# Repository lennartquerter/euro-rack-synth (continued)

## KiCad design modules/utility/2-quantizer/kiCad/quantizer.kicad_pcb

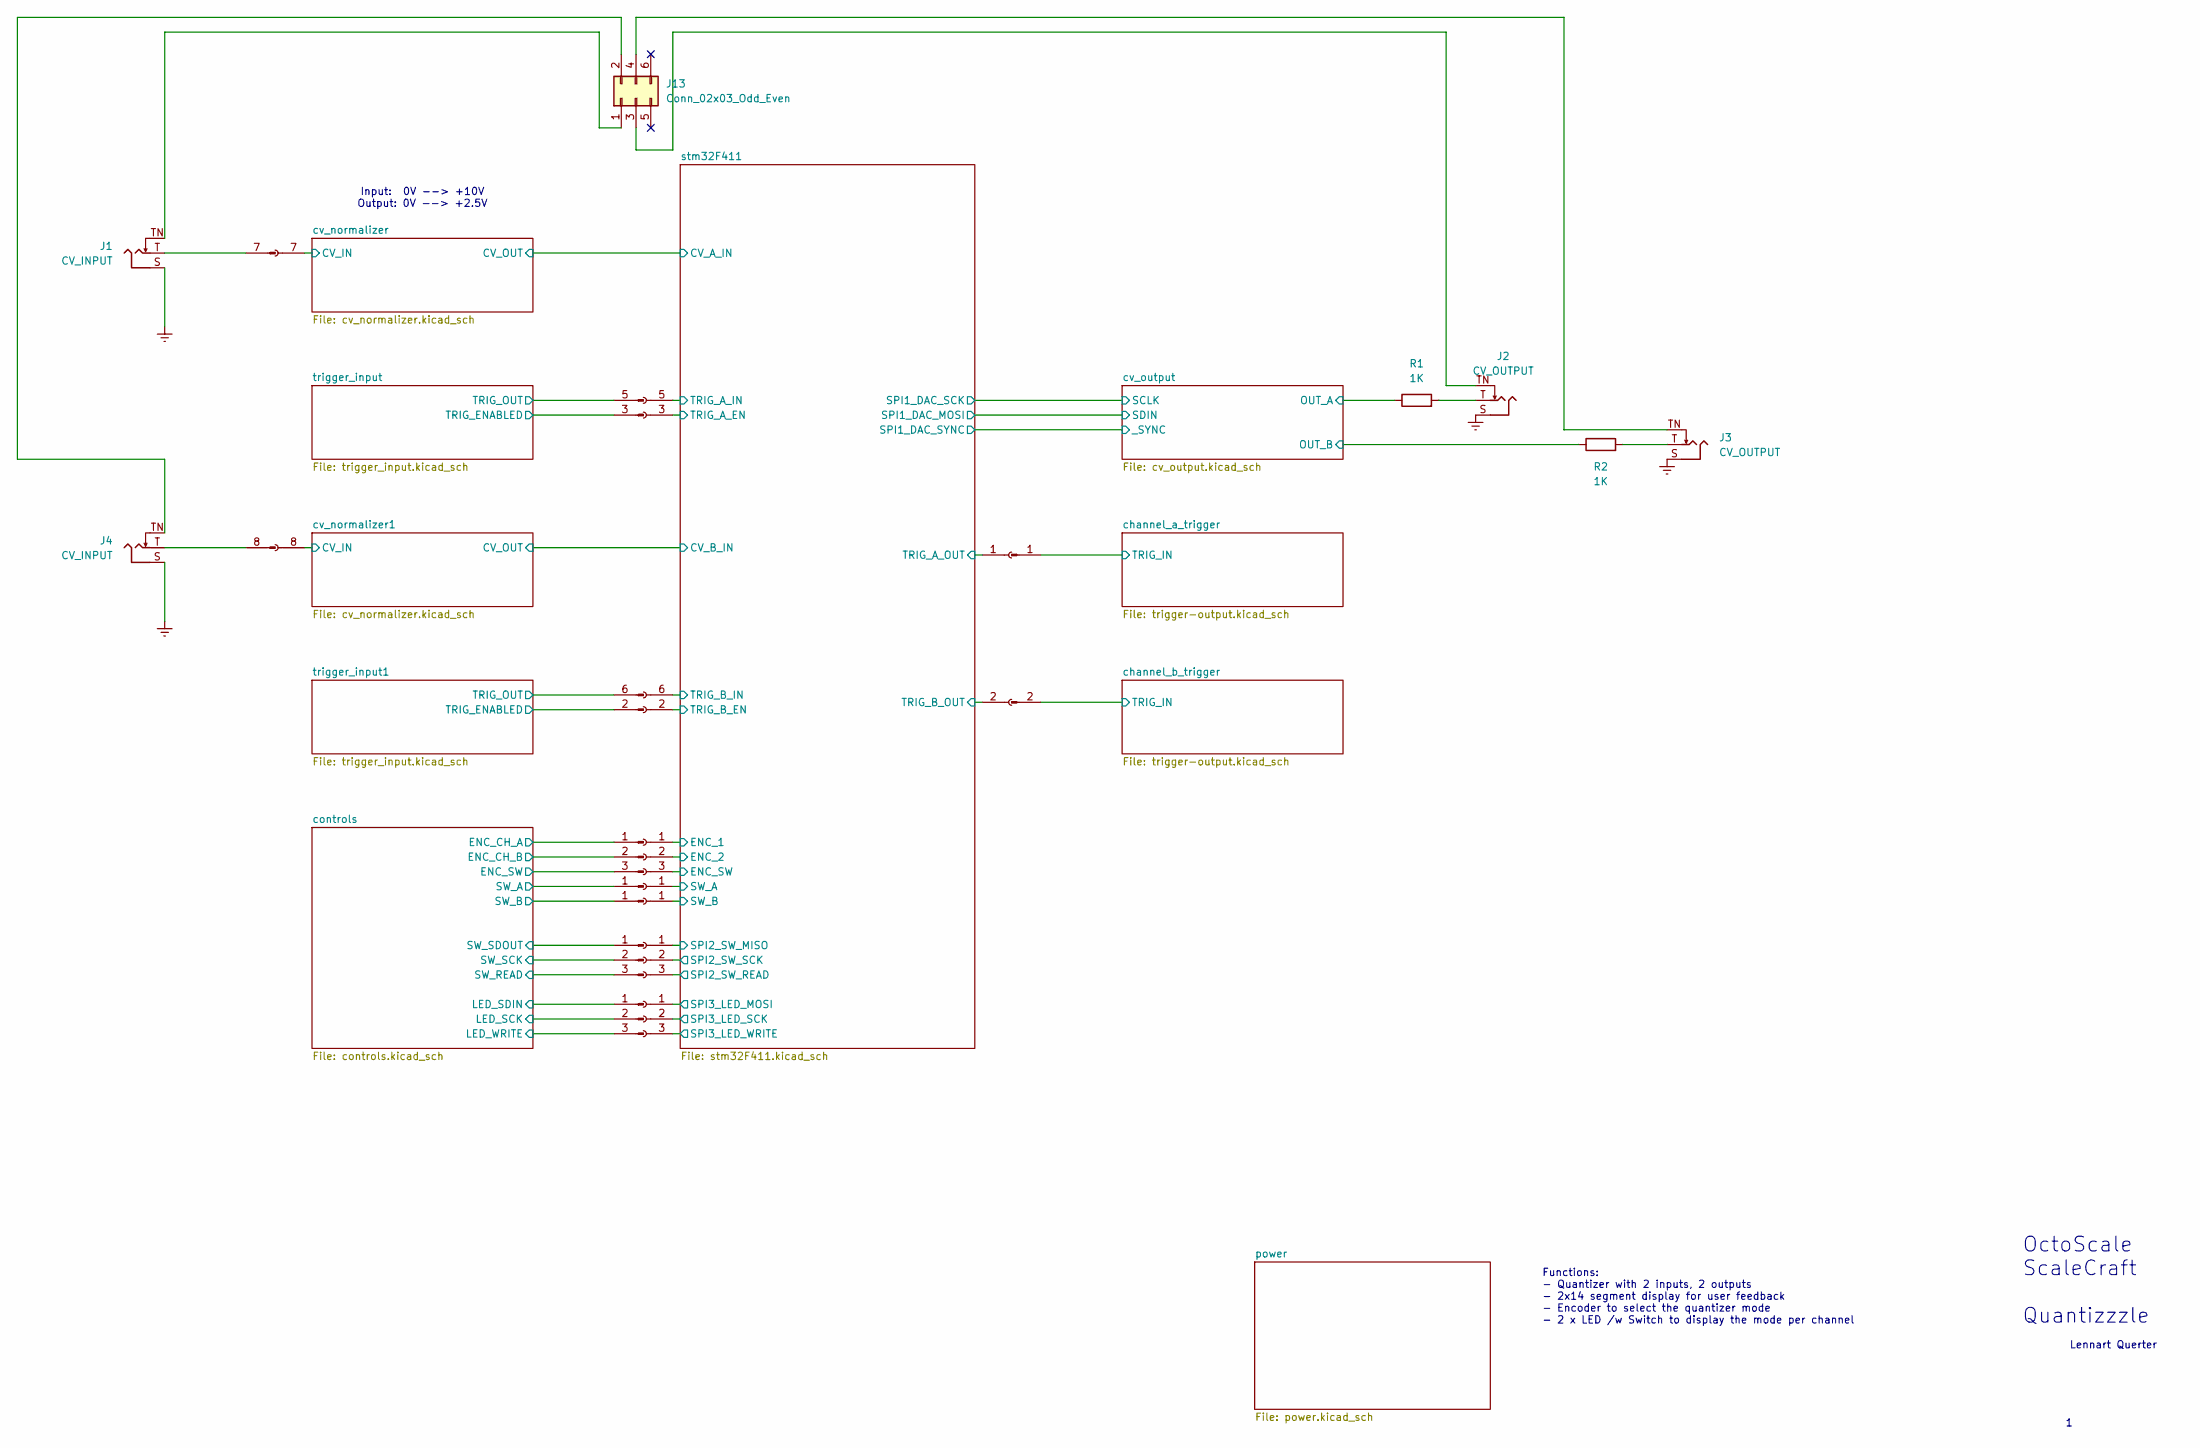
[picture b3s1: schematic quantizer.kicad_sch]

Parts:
J1, J4: CV_INPUT; Jack_3.5mm_QingPu_WQP-PJ398SM_Vertical_CircularHoles
J2, J3: CV_OUTPUT; Jack_3.5mm_QingPu_WQP-PJ398SM_Vertical_CircularHoles
J13: Conn_02x03_Odd_Even; PinHeader_2x03_P2.54mm_Vertical
R1, R2: 1K; R_0805_2012Metric_Pad1.20x1.40mm_HandSolder
XP1: Conn_01x08_Pin; PinHeader_1x08_P2.54mm_Vertical
XP2: Conn_01x08_Socket; PinSocket_1x08_P2.54mm_Vertical
XP3, XP6, XP8, XP9, XP12: Conn_01x04_Socket; PinSocket_1x04_P2.54mm_Vertical
XP4, XP5, XP7, XP10, XP11: Conn_01x04_Pin; PinHeader_1x04_P2.54mm_Vertical

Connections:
/channel_a_trigger/TRIG_IN: XP1.1; also elsewhere on the board
/channel_b_trigger/TRIG_IN: XP1.2; also elsewhere on the board
/controls/ENC_CH_A: XP11.1; also elsewhere on the board
/controls/ENC_CH_B: XP11.2; also elsewhere on the board
/controls/ENC_SW: XP11.3; also elsewhere on the board
/controls/LED_SCK: XP7.2; also elsewhere on the board
/controls/LED_SDIN: XP7.1; also elsewhere on the board
/controls/LED_WRITE: XP7.3; also elsewhere on the board
/controls/SW_A: XP5.1; also elsewhere on the board
/controls/SW_B: XP4.1; also elsewhere on the board
/controls/SW_READ: XP10.3; also elsewhere on the board
/controls/SW_SCK: XP10.2; also elsewhere on the board
/controls/SW_SDOUT: XP10.1; also elsewhere on the board
/cv_normalizer1/CV_IN: XP2.8; also elsewhere on the board
/cv_normalizer/CV_IN: XP2.7; also elsewhere on the board
/cv_output/OUT_A: R1.1; also elsewhere on the board
/cv_output/OUT_B: R2.1; also elsewhere on the board
/stm32F411/ENC_1: XP12.1; also elsewhere on the board
/stm32F411/ENC_2: XP12.2; also elsewhere on the board
/stm32F411/ENC_SW: XP12.3; also elsewhere on the board
/stm32F411/SPI2_SW_MISO: XP9.1; also elsewhere on the board
/stm32F411/SPI2_SW_READ: XP9.3; also elsewhere on the board
/stm32F411/SPI2_SW_SCK: XP9.2; also elsewhere on the board
/stm32F411/SPI3_LED_MOSI: XP8.1; also elsewhere on the board
/stm32F411/SPI3_LED_SCK: XP8.2; also elsewhere on the board
/stm32F411/SPI3_LED_WRITE: XP8.3; also elsewhere on the board
/stm32F411/SW_A: XP6.1; also elsewhere on the board
/stm32F411/SW_B: XP3.1; also elsewhere on the board
/stm32F411/TRIG_A_EN: XP6.3; also elsewhere on the board
/stm32F411/TRIG_A_IN: XP2.5; also elsewhere on the board
/stm32F411/TRIG_A_OUT: XP2.1; also elsewhere on the board
/stm32F411/TRIG_B_EN: XP6.2; also elsewhere on the board
/stm32F411/TRIG_B_IN: XP2.6; also elsewhere on the board
/stm32F411/TRIG_B_OUT: XP2.2; also elsewhere on the board
/trigger_input1/TRIG_ENABLED: XP5.2; also elsewhere on the board
/trigger_input1/TRIG_OUT: XP1.6; also elsewhere on the board
/trigger_input/TRIG_ENABLED: XP5.3; also elsewhere on the board
/trigger_input/TRIG_OUT: XP1.5; also elsewhere on the board
GNDREF: J1.S, J2.S, J3.S, J4.S; also elsewhere on the board
unnamed: J2.T, R1.2
unnamed: J3.T, R2.2
unnamed: J1.TN, J13.1
unnamed: J4.TN, J13.2
unnamed: J2.TN, J13.3
unnamed: J3.TN, J13.4
unnamed: J1.T, XP1.7
unnamed: J4.T, XP1.8

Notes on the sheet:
Input: 0V --> +10V Output: 0V --> +2.5V
OctoScale ScaleCraft Quantizzzle
Functions: - Quantizer with 2 inputs, 2 outputs - 2x14 segment display for user feedback - Encoder to select the quantizer mode - 2 x LED /w Switch to display the mode per channel
Lennart Querter

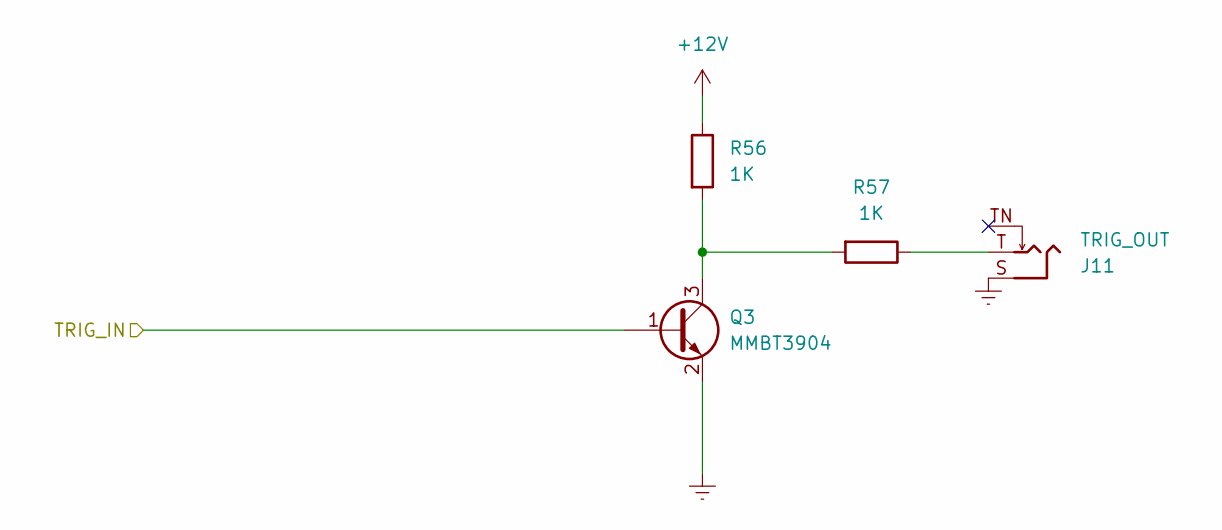
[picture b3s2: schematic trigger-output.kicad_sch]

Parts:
J11: TRIG_OUT; Jack_3.5mm_QingPu_WQP-PJ398SM_Vertical_CircularHoles
Q3: MMBT3904; SOT-23
R56, R57: 1K; R_0805_2012Metric_Pad1.20x1.40mm_HandSolder

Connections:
+12V: R56.1; also elsewhere on the board
/channel_a_trigger/TRIG_IN: Q3.1 (B); also elsewhere on the board
GNDREF: J11.S, Q3.2 (E); also elsewhere on the board
unnamed: J11.T, R57.1
unnamed: Q3.3 (C), R56.2, R57.2

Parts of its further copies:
J12: TRIG_OUT; Jack_3.5mm_QingPu_WQP-PJ398SM_Vertical_CircularHoles
Q4: MMBT3904; SOT-23
R59, R60: 1K; R_0805_2012Metric_Pad1.20x1.40mm_HandSolder

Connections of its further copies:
+12V: R59.1; also elsewhere on the board
/channel_b_trigger/TRIG_IN: Q4.1 (B); also elsewhere on the board
GNDREF: J12.S, Q4.2 (E); also elsewhere on the board
unnamed: J12.T, R60.1
unnamed: Q4.3 (C), R59.2, R60.2

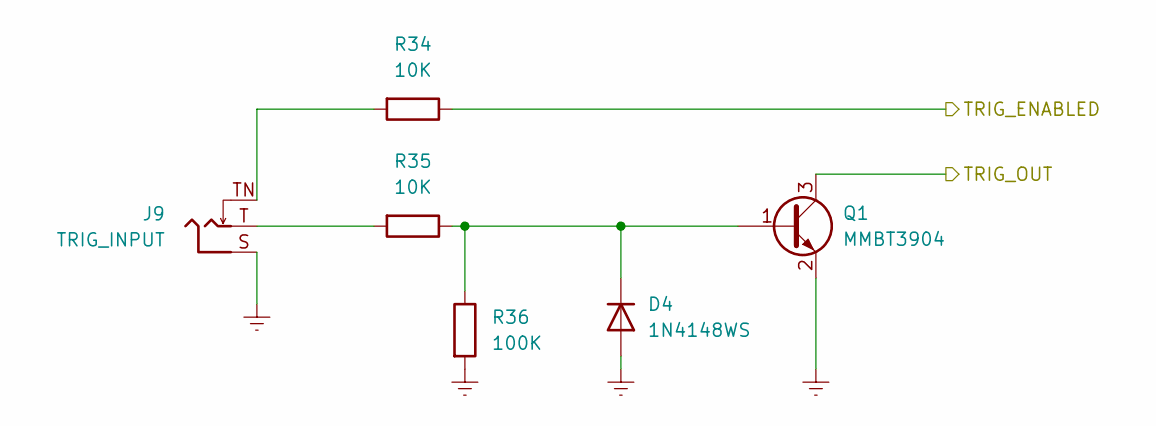
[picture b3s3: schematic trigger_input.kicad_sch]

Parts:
D4: 1N4148WS; D_SOD-323_HandSoldering
J9: TRIG_INPUT; Jack_3.5mm_QingPu_WQP-PJ398SM_Vertical_CircularHoles
Q1: MMBT3904; SOT-23
R34, R35: 10K; R_0805_2012Metric_Pad1.20x1.40mm_HandSolder
R36: 100K; R_0805_2012Metric_Pad1.20x1.40mm_HandSolder

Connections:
/trigger_input/TRIG_ENABLED: R34.1; also elsewhere on the board
/trigger_input/TRIG_OUT: Q1.3 (C); also elsewhere on the board
GNDREF: D4.2 (A), J9.S, Q1.2 (E), R36.2; also elsewhere on the board
unnamed: D4.1 (K), Q1.1 (B), R35.1, R36.1
unnamed: J9.T, R35.2
unnamed: J9.TN, R34.2

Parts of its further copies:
D9: 1N4148WS; D_SOD-323_HandSoldering
J10: TRIG_INPUT; Jack_3.5mm_QingPu_WQP-PJ398SM_Vertical_CircularHoles
Q2: MMBT3904; SOT-23
R53, R54: 10K; R_0805_2012Metric_Pad1.20x1.40mm_HandSolder
R55: 100K; R_0805_2012Metric_Pad1.20x1.40mm_HandSolder

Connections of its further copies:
/trigger_input1/TRIG_ENABLED: R53.1; also elsewhere on the board
/trigger_input1/TRIG_OUT: Q2.3 (C); also elsewhere on the board
GNDREF: D9.2 (A), J10.S, Q2.2 (E), R55.2; also elsewhere on the board
unnamed: D9.1 (K), Q2.1 (B), R54.1, R55.1
unnamed: J10.T, R54.2
unnamed: J10.TN, R53.2

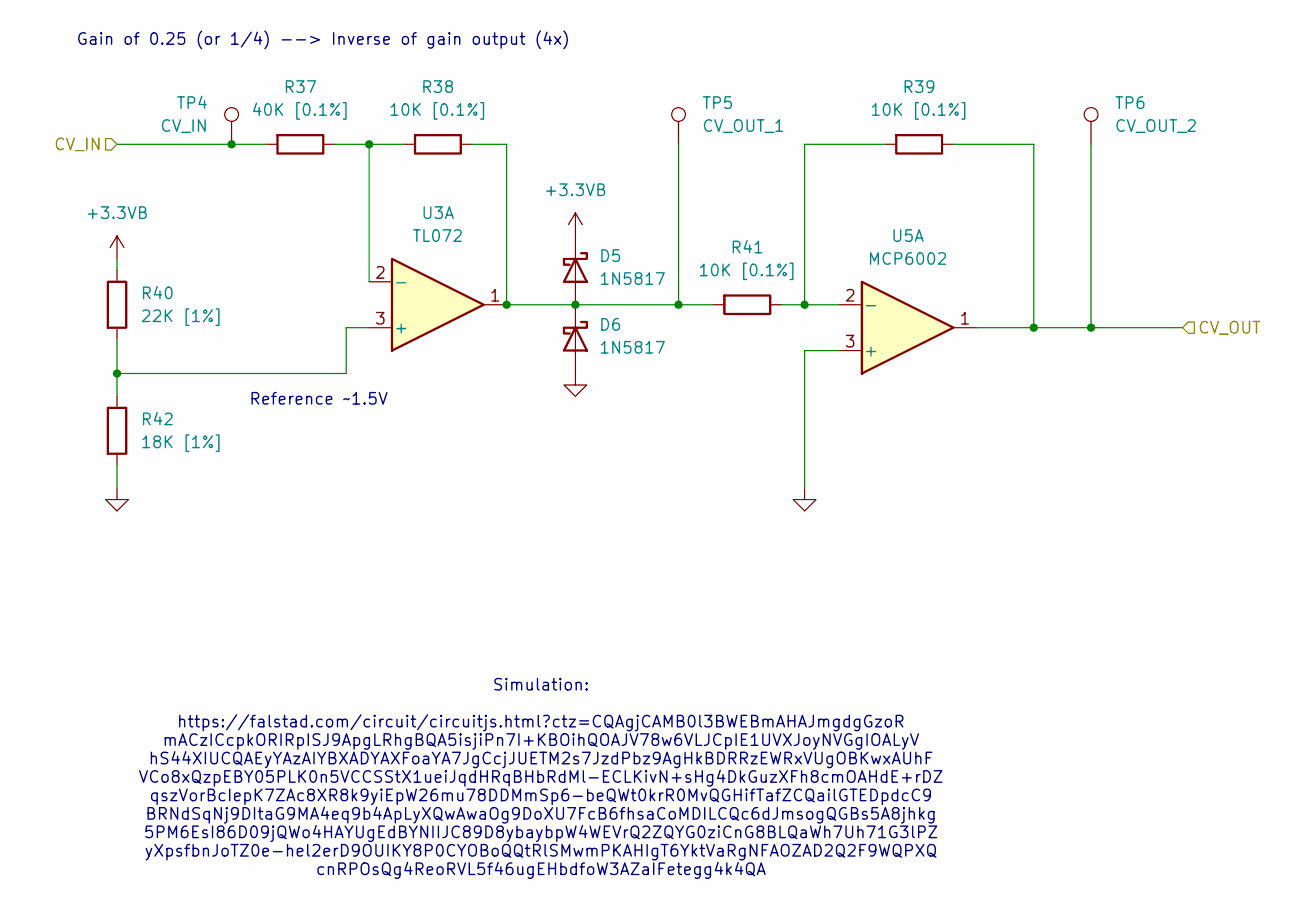
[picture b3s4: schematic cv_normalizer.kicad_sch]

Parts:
D5, D6: 1N5817; D_SOD-323_HandSoldering
R37: 40K [0.1%]; R_0805_2012Metric_Pad1.20x1.40mm_HandSolder
R38, R39, R41: 10K [0.1%]; R_0805_2012Metric_Pad1.20x1.40mm_HandSolder
R40: 22K [1%]; R_0805_2012Metric_Pad1.20x1.40mm_HandSolder
R42: 18K [1%]; R_0805_2012Metric_Pad1.20x1.40mm_HandSolder
TP4: CV_IN; TestPoint_Loop_D2.50mm_Drill1.0mm
TP5: CV_OUT_1; TestPoint_Loop_D2.50mm_Drill1.0mm
TP6: CV_OUT_2; TestPoint_Loop_D2.50mm_Drill1.0mm
U3: TL072; SOIC-8
U5: MCP6002; SOIC-8

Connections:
+3.3VB: D5.1 (K), R40.1; also elsewhere on the board
/cv_normalizer1/CV_OUT: U5.7; also elsewhere on the board
/cv_normalizer/CV_IN: R37.2, TP4.1; also elsewhere on the board
/cv_normalizer/CV_OUT: R39.1, TP6.1, U5.1; also elsewhere on the board
GND: D6.2 (A), R42.2, U5.3 (+), U5.5 (+); also elsewhere on the board
unnamed: D5.2 (A), D6.1 (K), R38.1, R41.2, TP5.1, U3.1
unnamed 69: U3.7; also elsewhere on the board
unnamed: R40.2, R42.1, U3.3 (+)
unnamed: R37.1, R38.2, U3.2 (-)
unnamed 115: U3.5 (+); also elsewhere on the board
unnamed 116: U3.6 (-); also elsewhere on the board
unnamed: R39.2, R41.1, U5.2 (-)
unnamed 122: U5.6 (-); also elsewhere on the board

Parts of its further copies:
D7, D8: 1N5817; D_SOD-323_HandSoldering
R47: 40K [0.1%]; R_0805_2012Metric_Pad1.20x1.40mm_HandSolder
R48, R49, R51: 10K [0.1%]; R_0805_2012Metric_Pad1.20x1.40mm_HandSolder
R50: 22K [1%]; R_0805_2012Metric_Pad1.20x1.40mm_HandSolder
R52: 18K [1%]; R_0805_2012Metric_Pad1.20x1.40mm_HandSolder
TP7: CV_IN; TestPoint_Loop_D2.50mm_Drill1.0mm
TP8: CV_OUT_1; TestPoint_Loop_D2.50mm_Drill1.0mm
TP9: CV_OUT_2; TestPoint_Loop_D2.50mm_Drill1.0mm

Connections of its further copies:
+3.3VB: D7.1 (K), R50.1; also elsewhere on the board
/cv_normalizer1/CV_IN: R47.2, TP7.1; also elsewhere on the board
/cv_normalizer1/CV_OUT: R49.1, TP9.1; also elsewhere on the board
GND: D8.2 (A), R52.2; also elsewhere on the board
unnamed 69: D7.2 (A), D8.1 (K), R48.1, R51.2, TP8.1; also elsewhere on the board
unnamed 115: R50.2, R52.1; also elsewhere on the board
unnamed 116: R47.1, R48.2; also elsewhere on the board
unnamed 122: R49.2, R51.1; also elsewhere on the board

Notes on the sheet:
Reference ~1.5V
Gain of 0.25 (or 1/4) --> Inverse of gain output (4x)
Simulation: https://falstad.com/circuit/circuitjs.html?ctz=CQAgjCAMB0l3BWEBmAHAJmgdgGzoR mACzICcpkORIRpISJ9ApgLRhgBQA5isjiPn7I+KBOihQOAJV78w6VLJCpIE1UVXJoyNVGgIOALyV hS44XIUCQAEyYAzAIYBXADYAXFoaYA7JgCcjJUETM2s7JzdPbz9AgHkBDRRzEWRxVUgOBKwxAUhF VCo8xQzpEBY05PLK0n5VCCSStX1ueiJqdHRqBHbRdMl-ECLKivN+sHg4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

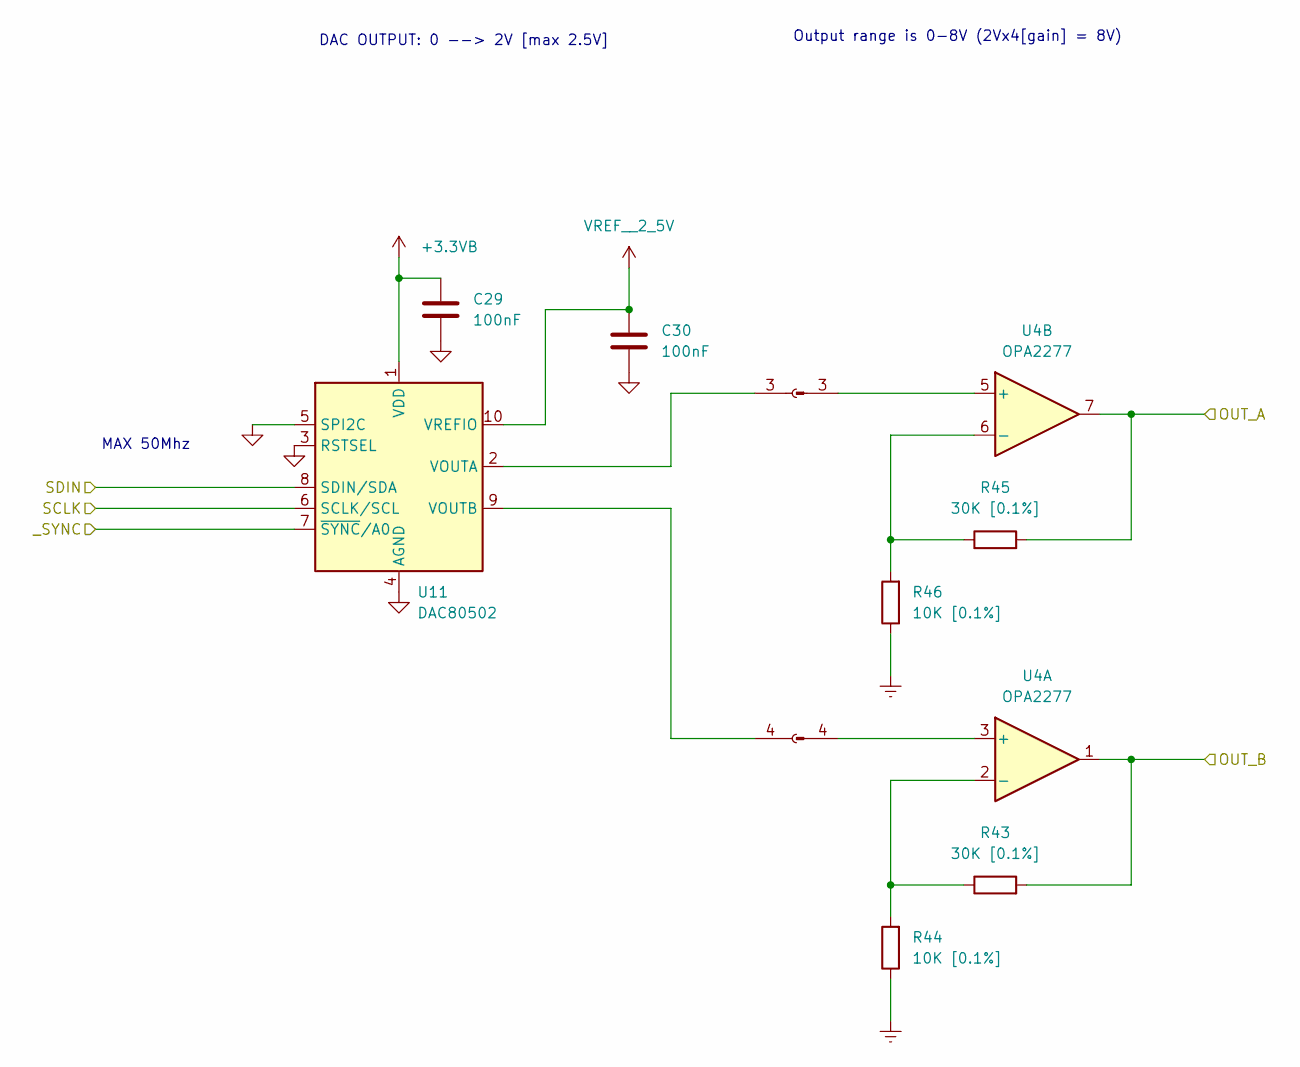
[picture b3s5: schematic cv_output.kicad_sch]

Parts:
C29, C30: 100nF; C_0805_2012Metric_Pad1.18x1.45mm_HandSolder
R43, R45: 30K [0.1%]; R_0805_2012Metric_Pad1.20x1.40mm_HandSolder
R44, R46: 10K [0.1%]; R_0805_2012Metric_Pad1.20x1.40mm_HandSolder
U4: OPA2277; SOIC-8
U11: DAC80502; DIP-10_W7.62mm_LongPads
XP1: Conn_01x08_Pin; PinHeader_1x08_P2.54mm_Vertical
XP2: Conn_01x08_Socket; PinSocket_1x08_P2.54mm_Vertical

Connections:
+3.3VB: C29.2, U11.1 (VDD); also elsewhere on the board
/cv_output/OUT_A: R45.2, U4.7; also elsewhere on the board
/cv_output/OUT_B: R43.2, U4.1; also elsewhere on the board
/cv_output/SCLK: U11.6 (SCLK/SCL); also elsewhere on the board
/cv_output/SDIN: U11.8 (SDIN/SDA); also elsewhere on the board
/cv_output/_SYNC: U11.7 (~SYNC/A0); also elsewhere on the board
GND: C29.1, C30.1, U11.3 (RSTSEL), U11.4 (AGND), U11.5 (SPI2C); also elsewhere on the board
GNDREF: R44.1, R46.1; also elsewhere on the board
unnamed: U4.3 (+), XP1.4
unnamed: R43.1, R44.2, U4.2 (-)
unnamed: U4.5 (+), XP1.3
unnamed: R45.1, R46.2, U4.6 (-)
unnamed: U11.2 (VOUTA), XP2.3
unnamed: U11.9 (VOUTB), XP2.4
VREF__2_5V: C30.2, U11.10 (VREFIO); also elsewhere on the board

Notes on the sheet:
Output range is 0-8V (2Vx4[gain] = 8V)
MAX 50Mhz
DAC OUTPUT: 0 --> 2V [max 2.5V]

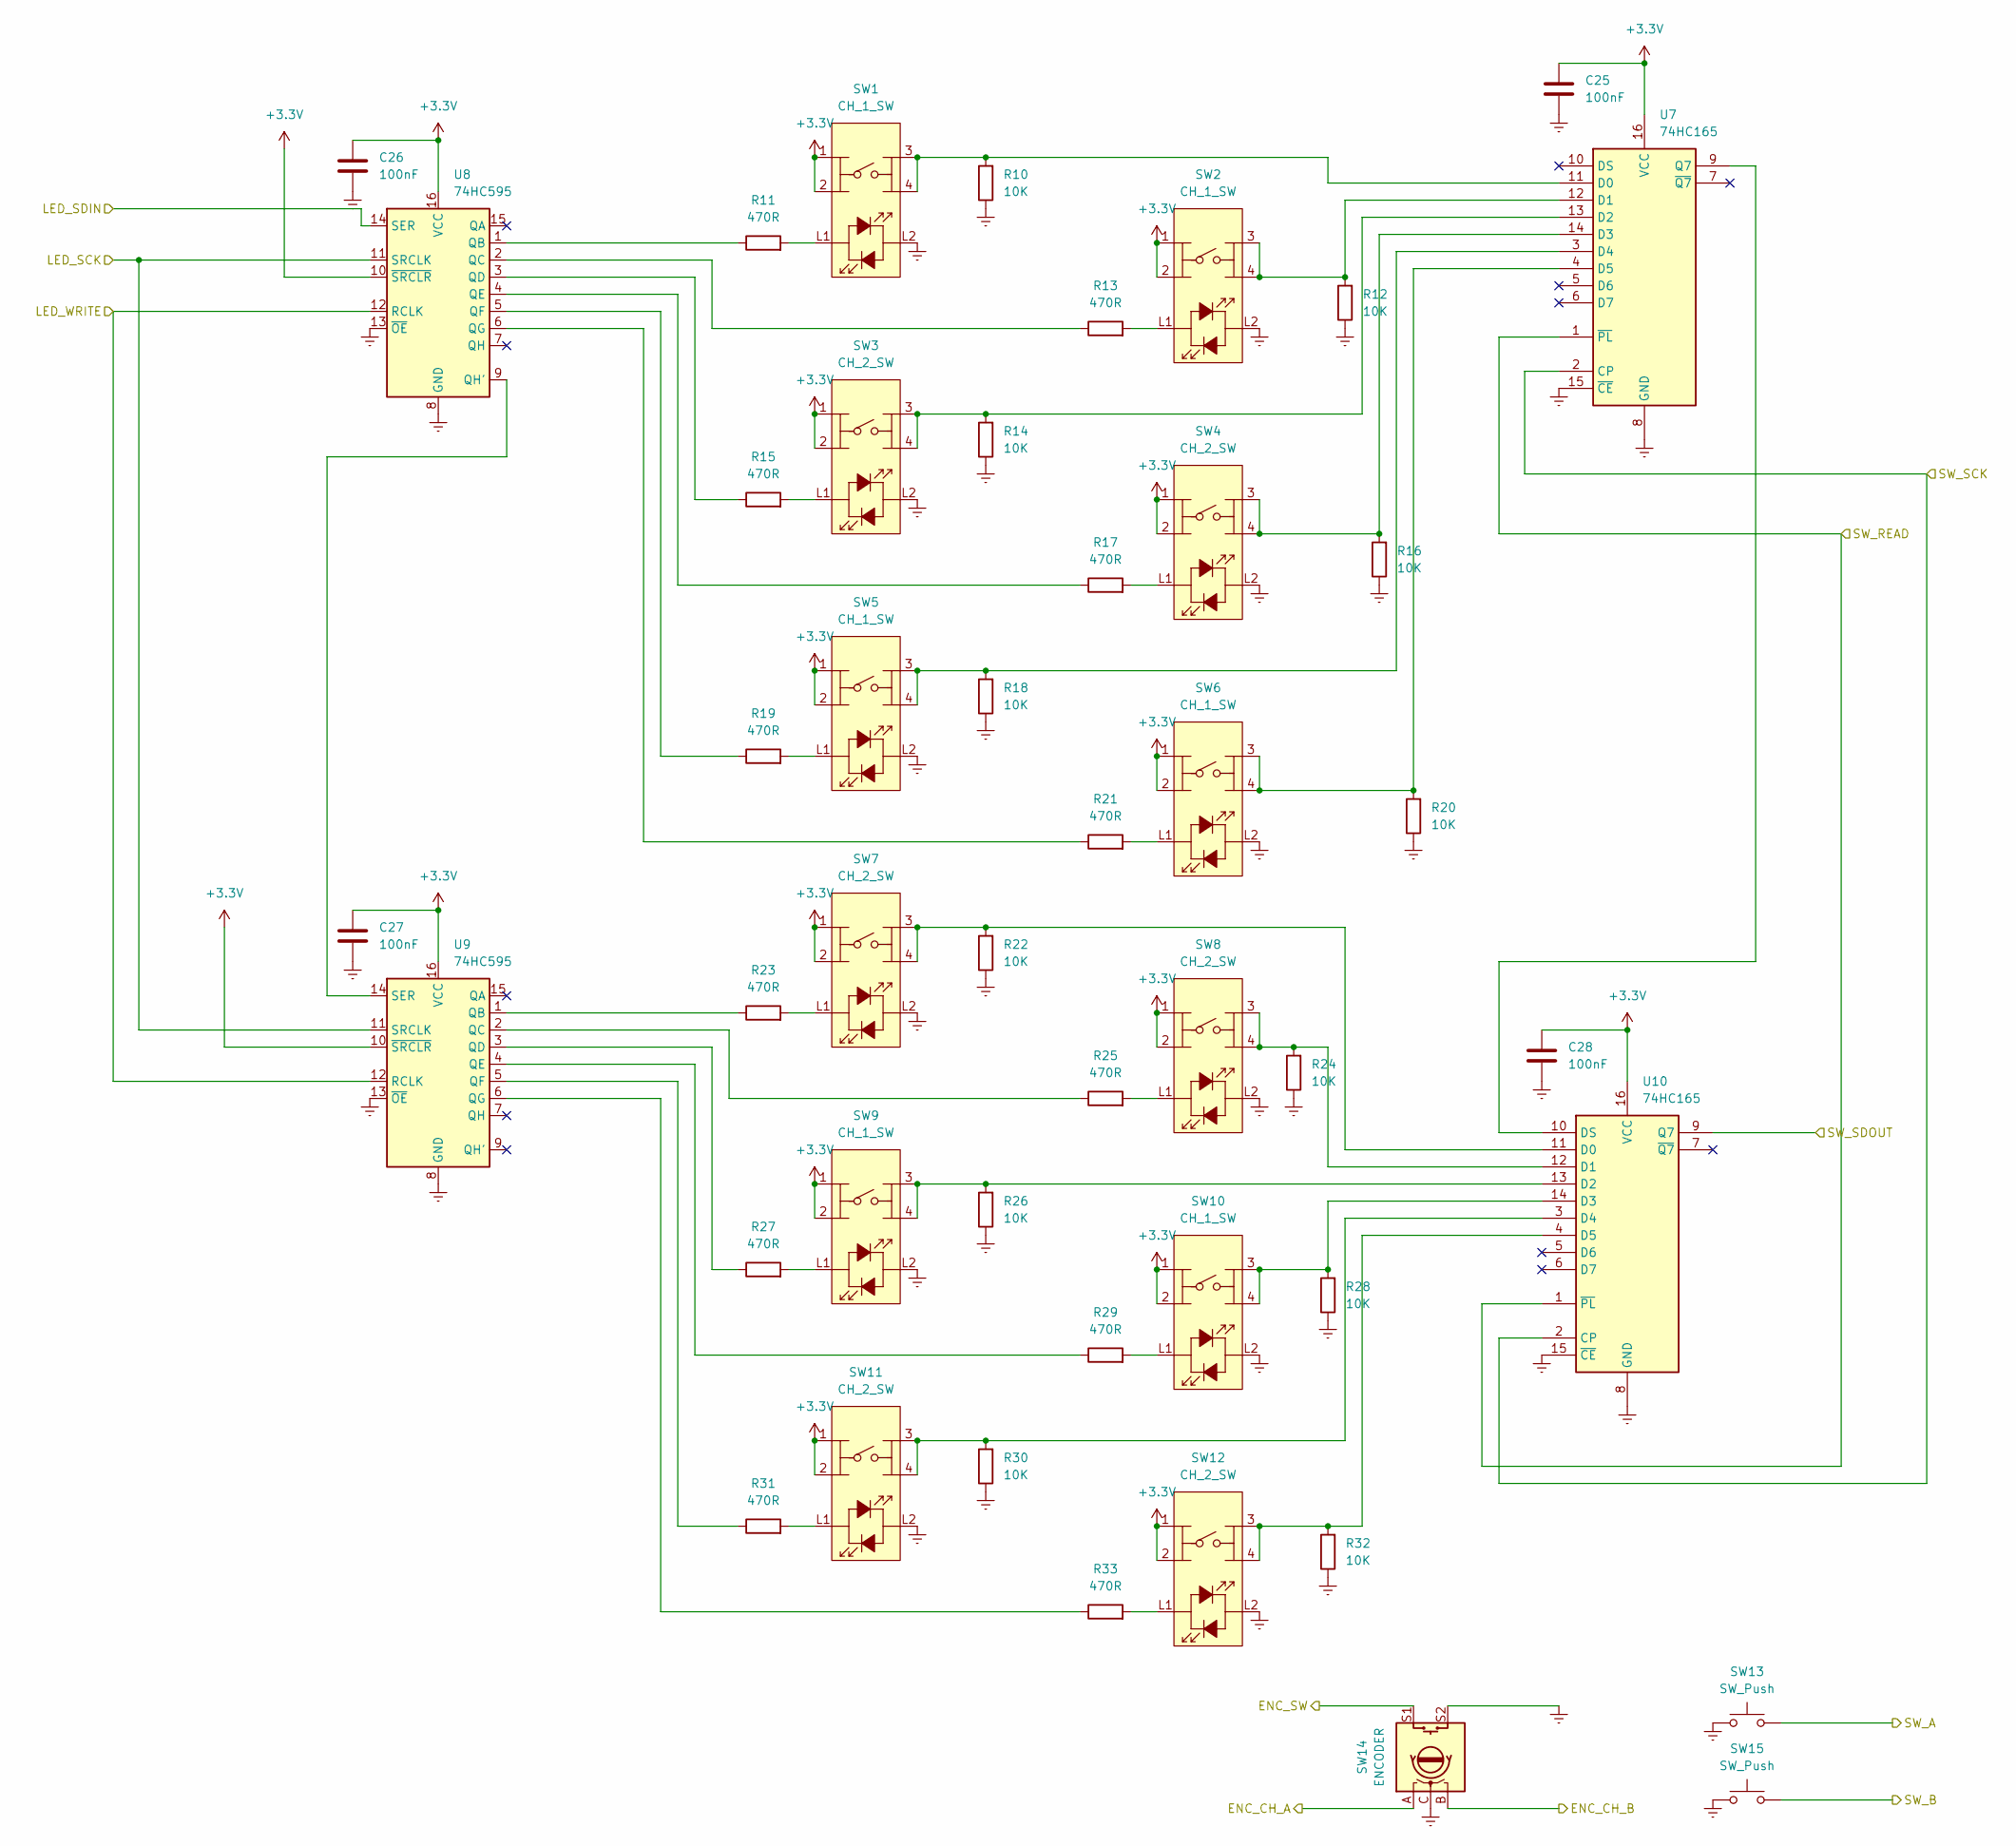
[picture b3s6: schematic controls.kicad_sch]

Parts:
C25, C26, C27, C28: 100nF; C_0805_2012Metric_Pad1.18x1.45mm_HandSolder
R10, R12, R14, R16, R18, R20, R22, R24, R26, R28, R30, R32: 10K; R_0805_2012Metric_Pad1.20x1.40mm_HandSolder
R11, R13, R15, R17, R19, R21, R23, R25, R27, R29, R31, R33: 470R; R_0805_2012Metric_Pad1.20x1.40mm_HandSolder
SW1, SW2, SW5, SW6, SW9, SW10: CH_1_SW; ML6-H2T2GQA
SW3, SW4, SW7, SW8, SW11, SW12: CH_2_SW; ML6-H2T2GQA
SW13, SW15: SW_Push; SW_PUSH_6mm
SW14: ENCODER; RotaryEncoder_Alps_EC11E-Switch_Vertical_H20mm_CircularMoun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
U7, U10: 74HC165; SOIC-16
U8, U9: 74HC595; SOIC-16

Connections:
+3.3V: C25.1, C26.1, C27.1, C28.1, SW1.1, SW1.2, SW2.1, SW2.2, SW3.1, SW3.2, SW4.1, SW4.2, SW5.1, SW5.2, SW6.1, SW6.2, SW7.1, SW7.2, SW8.1, SW8.2, SW9.1, SW9.2, SW10.1, SW10.2, SW11.1, SW11.2, SW12.1, SW12.2, U7.16 (VCC), U8.10 (~SRCLR), U8.16 (VCC), U9.10 (~SRCLR), U9.16 (VCC), U10.16 (VCC); also elsewhere on the board
/controls/ENC_CH_A: SW14.A; also elsewhere on the board
/controls/ENC_CH_B: SW14.B; also elsewhere on the board
/controls/ENC_SW: SW14.S1; also elsewhere on the board
/controls/LED_SCK: U8.11 (SRCLK), U9.11 (SRCLK); also elsewhere on the board
/controls/LED_SDIN: U8.14 (SER); also elsewhere on the board
/controls/LED_WRITE: U8.12 (RCLK), U9.12 (RCLK); also elsewhere on the board
/controls/SW_A: SW13.2; also elsewhere on the board
/controls/SW_B: SW15.2; also elsewhere on the board
/controls/SW_READ: U7.1 (~PL), U10.1 (~PL); also elsewhere on the board
/controls/SW_SCK: U7.2 (CP), U10.2 (CP); also elsewhere on the board
/controls/SW_SDOUT: U10.9 (Q7); also elsewhere on the board
/controls/unconnected-(U9-QH&amp;apos;-Pad9): U9.9 (QH')
GNDREF: C25.2, C26.2, C27.2, C28.2, R10.1, R12.1, R14.1, R16.1, R18.1, R20.1, R22.1, R24.1, R26.1, R28.1, R30.1, R32.1, SW1.L2, SW2.L2, SW3.L2, SW4.L2, SW5.L2, SW6.L2, SW7.L2, SW8.L2, SW9.L2, SW10.L2, SW11.L2, SW12.L2, SW13.1, SW14.C, SW14.S2, SW15.1, U7.8 (GND), U7.15 (~CE), U8.8 (GND), U8.13 (~OE), U9.8 (GND), U9.13 (~OE), U10.8 (GND), U10.15 (~CE); also elsewhere on the board
unnamed: R11.2, SW1.L1
unnamed: R13.2, SW2.L1
unnamed: R15.2, SW3.L1
unnamed: R17.2, SW4.L1
unnamed: R19.2, SW5.L1
unnamed: R21.2, SW6.L1
unnamed: R23.2, SW7.L1
unnamed: R25.2, SW8.L1
unnamed: R27.2, SW9.L1
unnamed: R29.2, SW10.L1
unnamed: R31.2, SW11.L1
unnamed: R33.2, SW12.L1
unnamed: R10.2, SW1.3, SW1.4 (A), U7.11 (D0)
unnamed: R12.2, SW2.3, SW2.4 (A), U7.12 (D1)
unnamed: R14.2, SW3.3, SW3.4 (A), U7.13 (D2)
unnamed: R16.2, SW4.3, SW4.4 (A), U7.14 (D3)
unnamed: R18.2, SW5.3, SW5.4 (A), U7.3 (D4)
unnamed: R20.2, SW6.3, SW6.4 (A), U7.4 (D5)
unnamed: R22.2, SW7.3, SW7.4 (A), U10.11 (D0)
unnamed: R24.2, SW8.3, SW8.4 (A), U10.12 (D1)
unnamed: R26.2, SW9.3, SW9.4 (A), U10.13 (D2)
unnamed: R28.2, SW10.3, SW10.4 (A), U10.14 (D3)
unnamed: R30.2, SW11.3, SW11.4 (A), U10.3 (D4)
unnamed: R32.2, SW12.3, SW12.4 (A), U10.4 (D5)
unnamed: R11.1, U8.1 (QB)
unnamed: R13.1, U8.2 (QC)
unnamed: R15.1, U8.3 (QD)
unnamed: R17.1, U8.4 (QE)
unnamed: R19.1, U8.5 (QF)
unnamed: R21.1, U8.6 (QG)
unnamed: U8.9 (QH'), U9.14 (SER)
unnamed: R23.1, U9.1 (QB)
unnamed: R25.1, U9.2 (QC)
unnamed: R27.1, U9.3 (QD)
unnamed: R29.1, U9.4 (QE)
unnamed: R31.1, U9.5 (QF)
unnamed: R33.1, U9.6 (QG)
unnamed: U7.9 (Q7), U10.10 (DS)

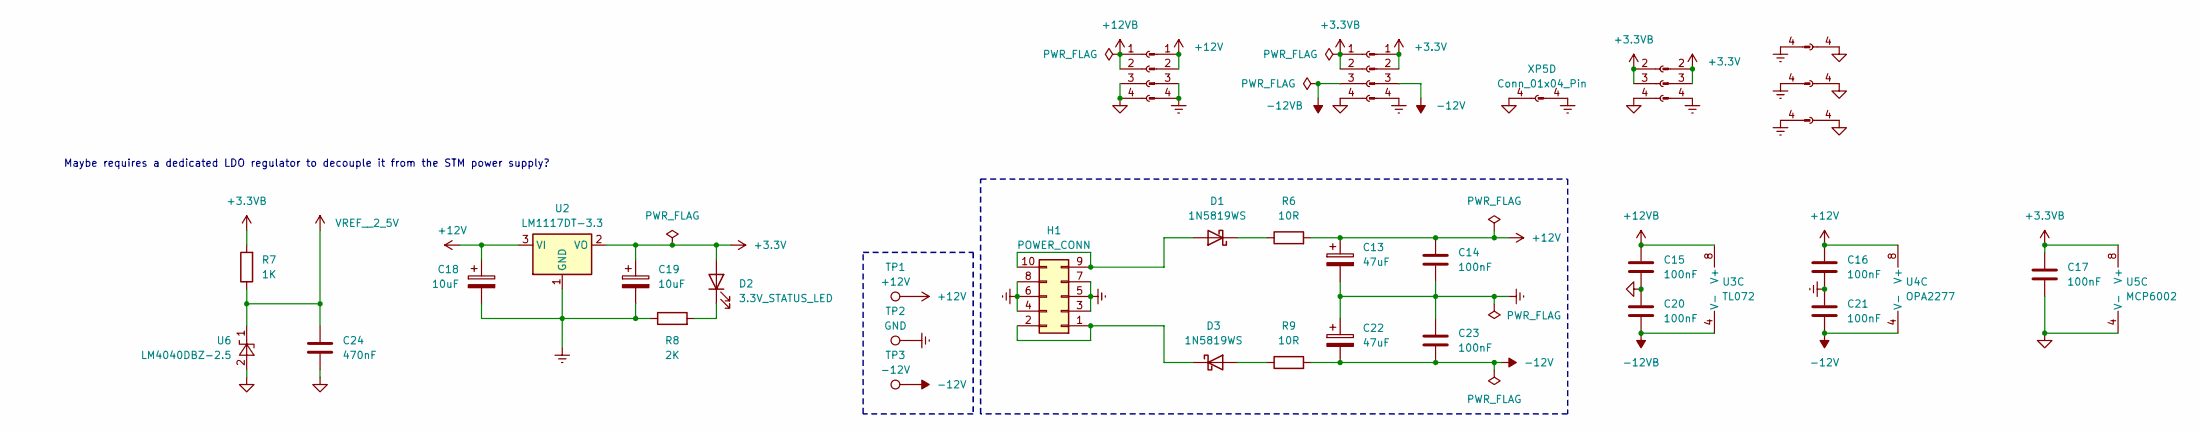
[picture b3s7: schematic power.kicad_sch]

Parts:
C13, C22: 47uF; CP_Radial_D6.3mm_P2.50mm
C14, C15, C16, C17, C20, C21, C23: 100nF; C_0805_2012Metric_Pad1.18x1.45mm_HandSolder
C18, C19: 10uF; CP_Radial_D4.0mm_P2.00mm
C24: 470nF; C_0805_2012Metric_Pad1.18x1.45mm_HandSolder
D1, D3: 1N5819WS; D_SOD-323_HandSoldering
D2: 3.3V_STATUS_LED; LED_0805_2012Metric_Pad1.15x1.40mm_HandSolder
H1: POWER_CONN; IDC-Header_2x05_P2.54mm_Vertical
R6, R9: 10R; R_0805_2012Metric_Pad1.20x1.40mm_HandSolder
R7: 1K; R_0805_2012Metric_Pad1.20x1.40mm_HandSolder
R8: 2K; R_0805_2012Metric_Pad1.20x1.40mm_HandSolder
TP1: +12V; Pin_D1.0mm_L10.0mm
TP2: GND; Pin_D1.0mm_L10.0mm
TP3: -12V; Pin_D1.0mm_L10.0mm
U2: LM1117DT-3.3; TO-252-3_TabPin2
U3: TL072; SOIC-8
U4: OPA2277; SOIC-8
U5: MCP6002; SOIC-8
U6: LM4040DBZ-2.5; SOT-23
XP3, XP6, XP8, XP9, XP12, XP14, XP15: Conn_01x04_Socket; PinSocket_1x04_P2.54mm_Vertical
XP4, XP5, XP7, XP10, XP11, XP13, XP16: Conn_01x04_Pin; PinHeader_1x04_P2.54mm_Vertical

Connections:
+3.3V: C19.1, D2.2 (A), U2.2 (VO), XP4.2, XP4.3, XP16.1, XP16.2; also elsewhere on the board
+3.3VB: C17.1, R7.2, U5.8 (V+), XP3.2, XP3.3, XP15.1, XP15.2; also elsewhere on the board
+12V: C13.1, C14.1, C16.1, C18.1, R6.2, TP1.1, U2.3 (VI), U4.8 (V+), XP13.1, XP13.2; also elsewhere on the board
+12VB: C15.1, U3.8 (V+), XP14.1, XP14.2
-12V: C21.2, C22.2, C23.2, R9.2, TP3.1, U4.4 (V-), XP16.3
-12VB: C20.2, U3.4 (V-), XP15.3
/cv_normalizer1/CV_OUT: U5.7; also elsewhere on the board
GND: C15.2, C17.2, C20.1, C24.2, U5.4 (V-), U5.5 (+), U6.2 (A), XP3.4, XP6.4, XP8.4, XP9.4, XP12.4, XP14.3, XP14.4, XP15.4; also elsewhere on the board
GNDREF: C13.2, C14.2, C16.2, C18.2, C19.2, C21.1, C22.1, C23.1, H1.3, H1.4, H1.5, H1.6, H1.7, H1.8, R8.1, TP2.1, U2.1 (GND), XP4.4, XP5.4, XP7.4, XP10.4, XP11.4, XP13.3, XP13.4, XP16.4; also elsewhere on the board
unnamed: D1.2 (A), H1.9, H1.10
unnamed: D1.1 (K), R6.1
unnamed: D2.1 (K), R8.2
unnamed: D3.2 (A), R9.1
unnamed: D3.1 (K), H1.1, H1.2
unnamed 69: U3.7; also elsewhere on the board
unnamed 115: U3.5 (+); also elsewhere on the board
unnamed 116: U3.6 (-); also elsewhere on the board
unnamed 122: U5.6 (-); also elsewhere on the board
VREF__2_5V: C24.1, R7.1, U6.1 (K); also elsewhere on the board

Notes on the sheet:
Maybe requires a dedicated LDO regulator to decouple it from the STM power supply?
